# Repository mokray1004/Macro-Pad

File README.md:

# Macro-Pad
So this is a small form factor 16 key macro pad that has a 1:1 aspect ratio along with a rotatable and clickable knob.
This uses the ZMK firmware.
Files for materials and other things are in the rest of the repo. You can do whatever you want to it.
Here is the 3d model of the whole project so you get an image of what it should look like:

[3D model](CAD/image.png)

bro the files were here the entire time heres a link to them on the repository:

[PCB file](CAD/macropadpcb.kicad_pcb)

[PCB schematics](CAD/macropadpcb.kicad_sch)

[Other PCB file](CAD/macropadpcb.kicad_pro)

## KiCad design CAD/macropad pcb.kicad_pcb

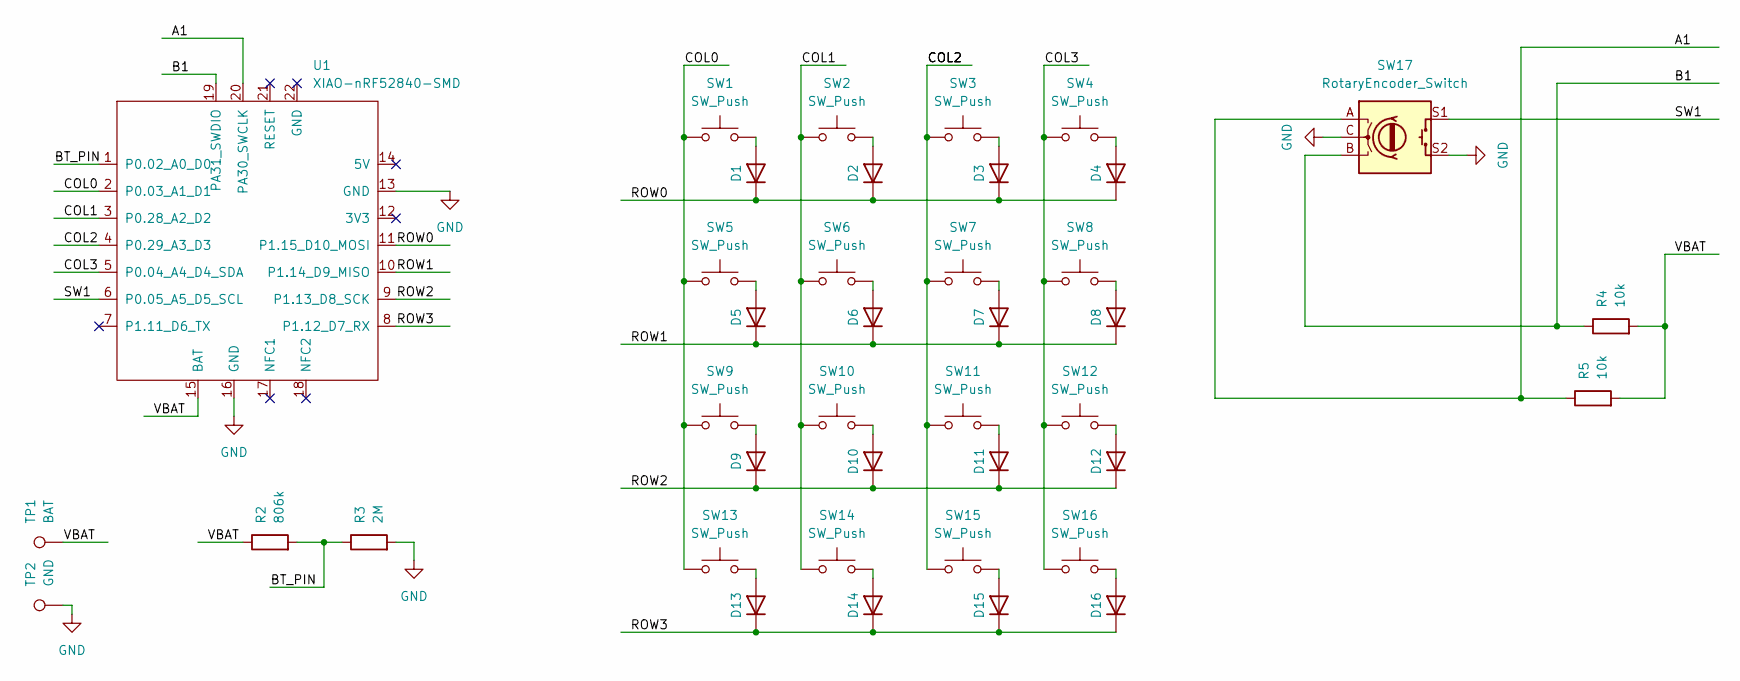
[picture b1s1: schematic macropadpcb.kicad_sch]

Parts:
D1, D2, D3, D4, D5, D6, D7, D8, D9, D10, D11, D12, D13, D14, D15, D16: D; D_SOD-123
R2: 806k; R_0805_2012Metric
R3: 2M; R_0805_2012Metric
R4, R5: 10k; R_0805_2012Metric
SW1, SW2, SW3, SW4, SW5, SW6, SW7, SW8, SW9, SW10, SW11, SW12, SW13, SW14, SW15, SW16: SW_Push; SW_Cherry_MX_1.00u_PCB
SW17: RotaryEncoder_Switch; RotaryEncoder_Alps_EC11E-Switch_Vertical_H20mm
TP1: BAT; TestPoint_Pad_D2.0mm
TP2: GND; TestPoint_Pad_D2.0mm
U1: XIAO-nRF52840-SMD; modified-XIAO-nRF52840-SMD

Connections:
/A1: R5.1, SW17.A, U1.20 (PA30_SWCLK)
/B1: R4.1, SW17.B, U1.19 (PA31_SWDIO)
/BT_PIN: R2.2, R3.1, U1.1 (P0.02_A0_D0)
/COL0: SW1.1, SW5.1, SW9.1, SW13.1, U1.2 (P0.03_A1_D1)
/COL1: SW2.1, SW6.1, SW10.1, SW14.1, U1.3 (P0.28_A2_D2)
/COL2: SW3.1, SW7.1, SW11.1, SW15.1, U1.4 (P0.29_A3_D3)
/COL3: SW4.1, SW8.1, SW12.1, SW16.1, U1.5 (P0.04_A4_D4_SDA)
/ROW0: D1.1 (K), D2.1 (K), D3.1 (K), D4.1 (K), U1.11 (P1.15_D10_MOSI)
/ROW1: D5.1 (K), D6.1 (K), D7.1 (K), D8.1 (K), U1.10 (P1.14_D9_MISO)
/ROW2: D9.1 (K), D10.1 (K), D11.1 (K), D12.1 (K), U1.9 (P1.13_D8_SCK)
/ROW3: D13.1 (K), D14.1 (K), D15.1 (K), D16.1 (K), U1.8 (P1.12_D7_RX)
/SW1: SW17.S1, U1.6 (P0.05_A5_D5_SCL)
/VBAT: R2.1, R4.2, R5.2, TP1.1, U1.15 (BAT)
GND: R3.2, SW17.C, SW17.S2, TP2.1, U1.13 (GND), U1.16 (GND)
unnamed: D1.2 (A), SW1.2
unnamed: D2.2 (A), SW2.2
unnamed: D3.2 (A), SW3.2
unnamed: D4.2 (A), SW4.2
unnamed: D5.2 (A), SW5.2
unnamed: D6.2 (A), SW6.2
unnamed: D7.2 (A), SW7.2
unnamed: D8.2 (A), SW8.2
unnamed: D9.2 (A), SW9.2
unnamed: D10.2 (A), SW10.2
unnamed: D11.2 (A), SW11.2
unnamed: D12.2 (A), SW12.2
unnamed: D13.2 (A), SW13.2
unnamed: D14.2 (A), SW14.2
unnamed: D15.2 (A), SW15.2
unnamed: D16.2 (A), SW16.2

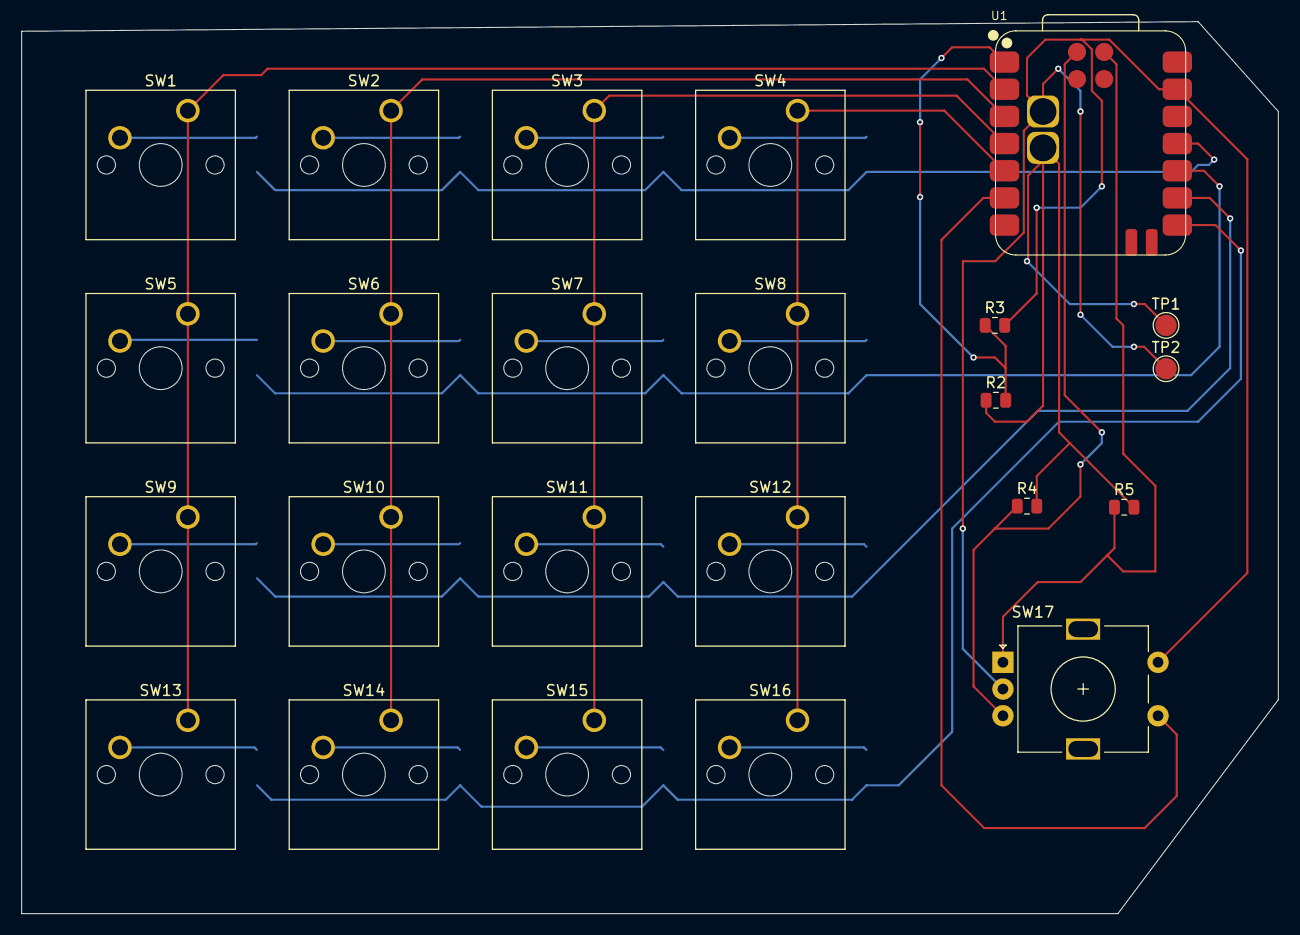
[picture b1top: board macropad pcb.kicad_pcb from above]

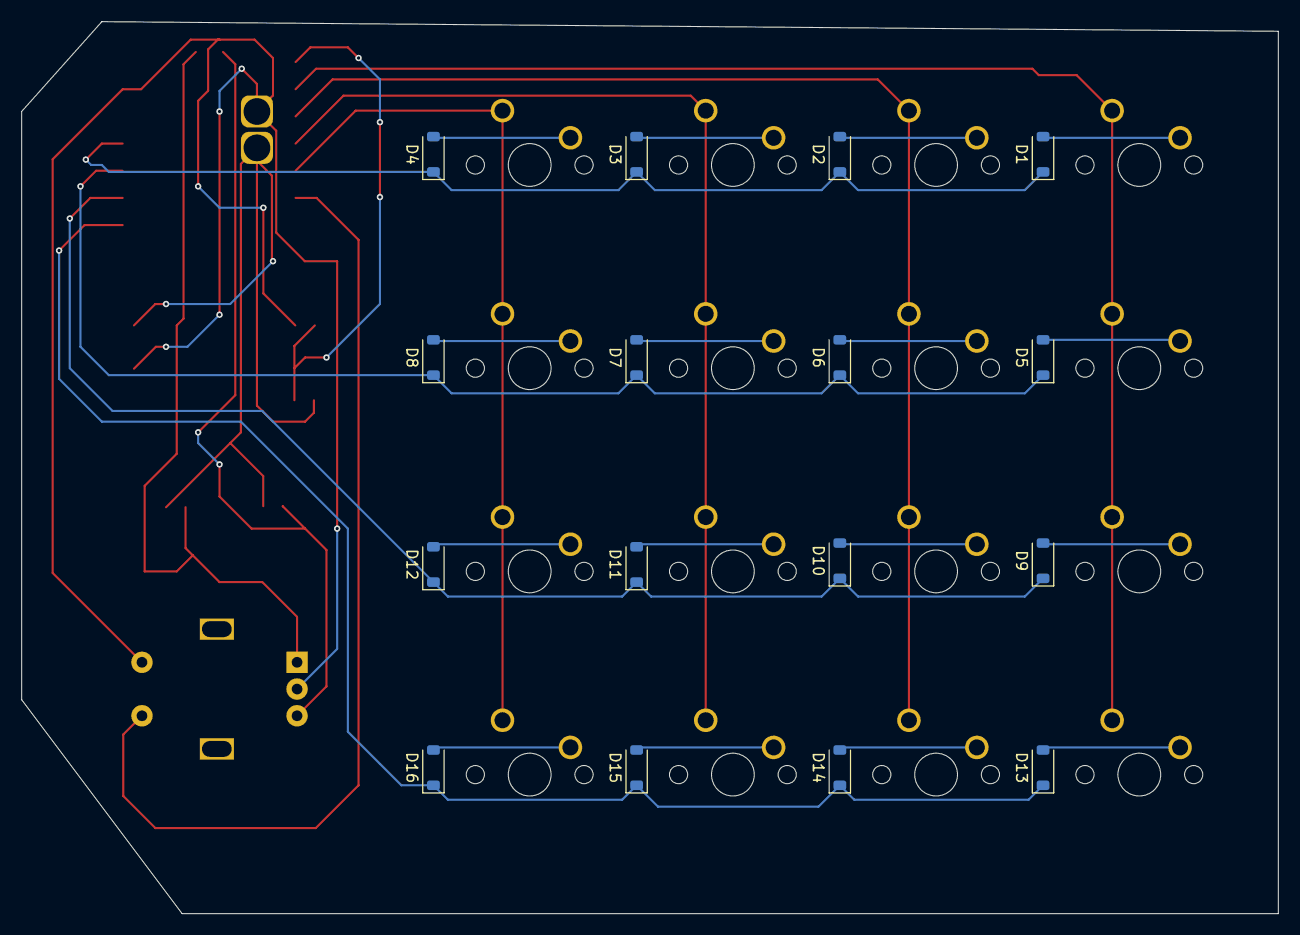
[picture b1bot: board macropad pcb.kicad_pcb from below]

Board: 2 copper layers, 117.5 x 83.4 mm, 40 parts (16 on the bottom side), 30 nets.

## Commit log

2026-03-10 Create h
2026-03-10 Rename WhatsApp Image 2026-03-09 at 18.17.44.jpeg to PCB Layout v0.2
2026-03-10 Create j
2026-03-10 Create BOM
2026-03-11 Update BOM
2026-03-16 Rename Macro.zip to Macropad PCB Gerber.zip
2026-03-16 Rename macropad pcb.kicad_pro to macropadpcb.kicad_pro
2026-03-16 Rename macropad pcb.kicad_sch to macropadpcb.kicad_sch
2026-03-16 Rename macropad pcb.kicad_pcb to macropadpcb.kicad_pcb
